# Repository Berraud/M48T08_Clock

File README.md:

# M48T08_Clock
Reloj con RTC M48T08 y ATMEGA328

Reloj diseñado en torno a un display 5-LT-02/02m, un RTC paralelo M48T08 y un ATMEGA328.

Procedimiento para setear la hora:

1) completar los registros con la fecha actual y la hora con algunos minutos a futuro

byte registros[8][8]={{0,0,0,1,1,0,0,1},//año 
                      {0,0,0,0,0,0,1,1},//mes
                      {0,0,1,0,0,0,1,1},//dia 
                      {0,0,0,0,0,1,1,0},//dia semana 
                      {0,0,0,1,0,0,0,1},//horas
                      {0,0,1,1,0,1,0,1},//minutos 
                      {1,0,0,0,0,0,0,0},//segundos
                      {0,0,0,0,0,0,0,0}};//cal
                      
Según hoja de datos el bit más significativo del registro segundos debe ser puesto en 1 primero y en 0 después para asegurar que el RTC comience a correr. Así que se puede cargar eso así sin configurar la hora, y después pasarlo a 0.

2) cargar código
3) Esperar a que sea la hora seteada en los registros y resetear el micro

Nota: No es nada elegante, podría hacerse mediante un menú por serie, o lo que sea, pero funciona y es rápido. Ver pines de conexión en el código. Lo hice con un Mega por disponibilidad de pines, pero podría hacerse también con un Nano

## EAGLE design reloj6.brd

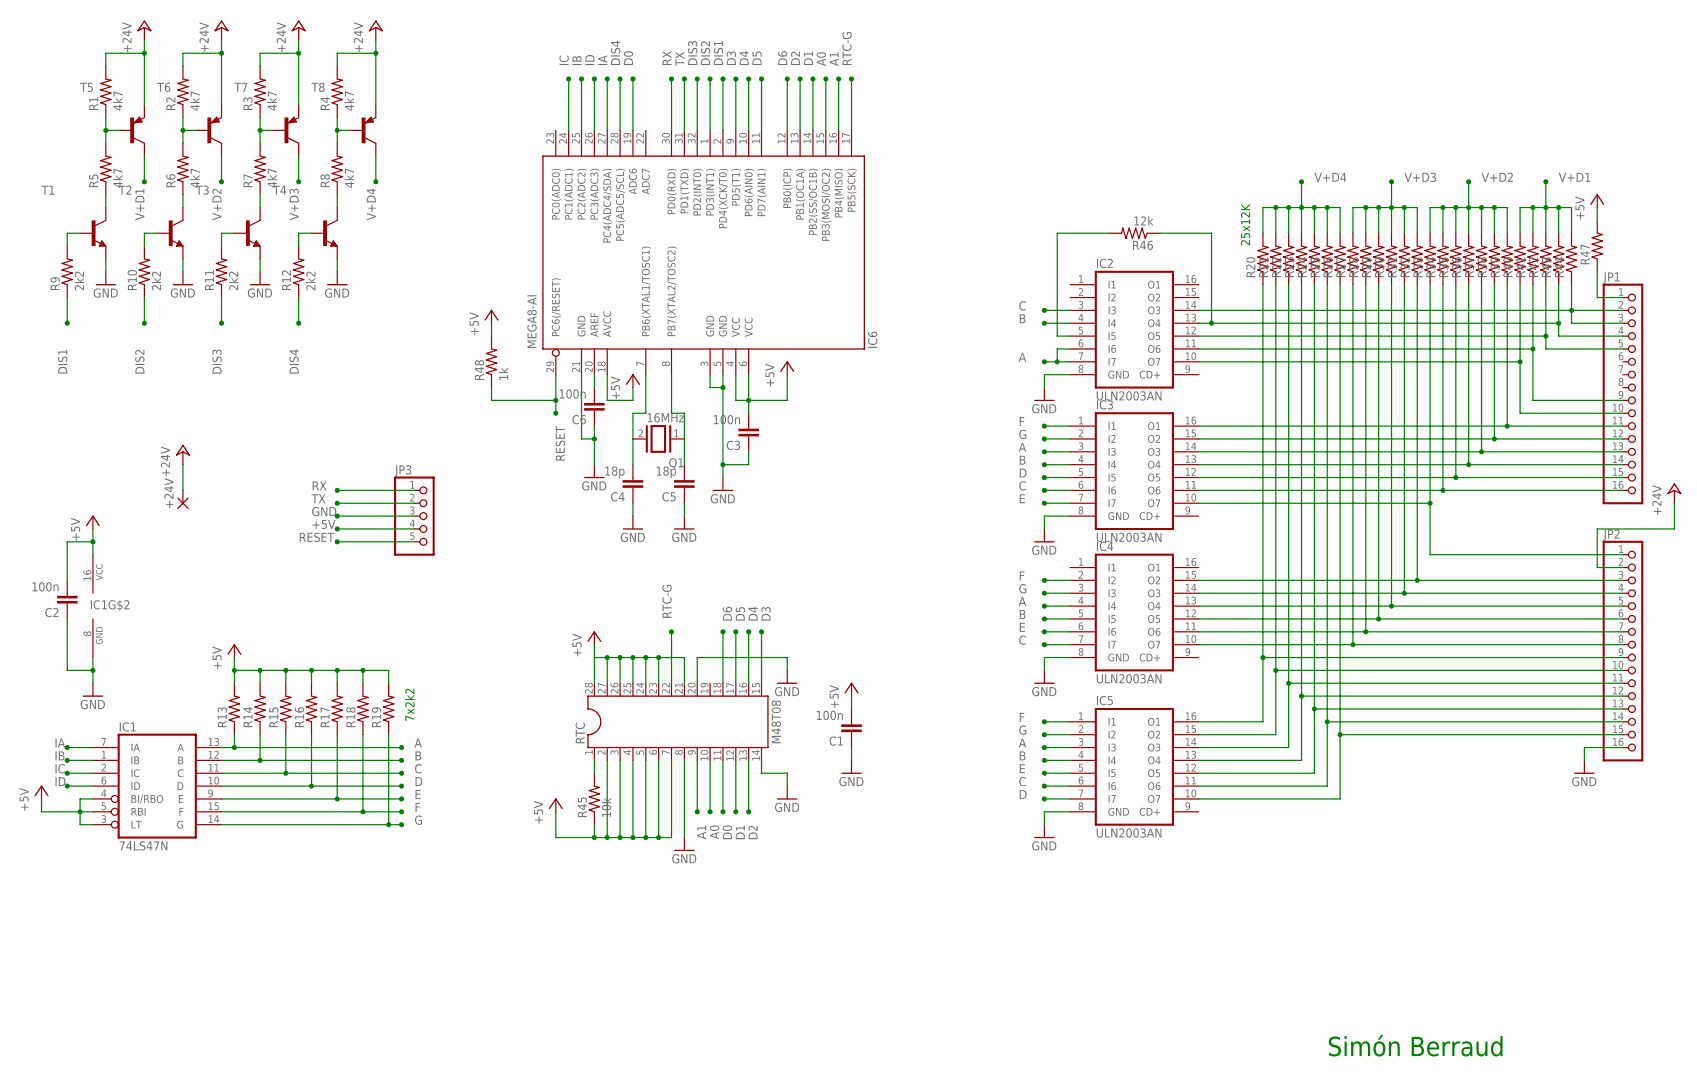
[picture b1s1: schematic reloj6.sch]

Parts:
+24V: 2,54/0,8
C1, C2, C3: 100n; C025-025X050
C4, C5: 18p; C0805K
C6: 100n; C0805K
IC1: 74LS47N; DIL16
IC2, IC3, IC4, IC5: ULN2003AN; DIL16
IC6: MEGA8-AI; TQFP32-08
JP1, JP2: PINHD-1X16; 1X16
JP3: PINHD-1X5; 1X05
Q1: 16MHz; QS
R1, R2, R3, R4, R5, R6, R7, R8: 4k7; 0207/7
R9, R10, R11, R12: 2k2; 0207/7
R13, R14, R15, R16, R17, R18, R19, R20, R21, R22, R23, R24, R25, R26, R27, R28, R29, R30, R31, R32, R33, R34, R35, R36, R37, R38, R39, R40, R41, R42, R43, R44: R-US_0207/7; 0207/7
R45: 10k; 0207/7
R46: 12k; 0207/7
R47: R-US_0411/12; 0411/12
R48: 1k; R1206
RTC: M48T08; DIL28-6
T1, T2, T3, T4: BC169-NPN-TO92-ECB; TO92-ECB
T5, T6, T7, T8: -PNP-TO92-ECB; TO92-ECB

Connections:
+5V: C1.2, C2.2, C3.2, IC1.3 (LT), IC1.4 (BI/RBO), IC1.5 (RBI), IC1.16 (VCC), IC6.4 (VCC), IC6.6 (VCC), IC6.18 (AVCC), JP3.4, R13.2, R14.2, R15.2, R16.2, R17.2, R18.2, R19.2, R45.1, R47.2, R48.2, RTC.2, RTC.3, RTC.4, RTC.5, RTC.6, RTC.7, RTC.21, RTC.23, RTC.24, RTC.25, RTC.26, RTC.27, RTC.28
+24V: +24V.1, JP2.2, R1.2, R2.2, R3.2, R4.2, T5.E, T6.E, T7.E, T8.E
A: IC1.13 (A), IC2.6 (I6), IC2.7 (I7), IC3.3 (I3), IC4.4 (I4), IC5.3 (I3), R13.1
A0: IC6.15 (PB3(MOSI/OC2)), RTC.10
A1: IC6.16 (PB4(MISO)), RTC.9
B: IC1.12 (B), IC2.4 (I4), IC3.4 (I4), IC4.5 (I5), IC5.4 (I4), R14.1
C: IC1.11 (C), IC2.3 (I3), IC3.6 (I6), IC4.7 (I7), IC5.6 (I6), R15.1
D: IC1.10 (D), IC3.5 (I5), IC5.7 (I7), R16.1
D0: IC6.19 (ADC6), RTC.11
D1: IC6.14 (PB2(SS/OC1B)), RTC.12
D2: IC6.13 (PB1(OC1A)), RTC.13
D3: IC6.9 (PD5(T1)), RTC.15
D4: IC6.10 (PD6(AIN0)), RTC.16
D5: IC6.11 (PD7(AIN1)), RTC.17
D6: IC6.12 (PB0(ICP)), RTC.18
DIS1: IC6.2 (PD4(XCK/T0)), R9.1
DIS2: IC6.1 (PD3(INT1)), R10.1
DIS3: IC6.32 (PD2(INT0)), R11.1
DIS4: IC6.28 (PC5(ADC5/SCL)), R12.1
E: IC1.9 (E), IC3.7 (I7), IC4.6 (I6), IC5.5 (I5), R17.1
F: IC1.15 (F), IC3.1 (I1), IC4.2 (I2), IC5.1 (I1), R18.1
G: IC1.14 (G), IC3.2 (I2), IC4.3 (I3), IC5.2 (I2), R19.1
GND: C1.1, C2.1, C3.1, C4.1, C5.1, C6.1, IC1.8 (GND), IC2.8 (GND), IC3.8 (GND), IC4.8 (GND), IC5.8 (GND), IC6.3 (GND), IC6.5 (GND), IC6.21 (GND), JP2.16, JP3.3, RTC.8, RTC.14, RTC.20, T1.E, T2.E, T3.E, T4.E
IA: IC1.7 (IA), IC6.27 (PC4(ADC4/SDA))
IB: IC1.1 (IB), IC6.25 (PC2(ADC2))
IC: IC1.2 (IC), IC6.24 (PC1(ADC1))
ID: IC1.6 (ID), IC6.26 (PC3(ADC3))
unnamed: R9.2, T1.B
unnamed: R10.2, T2.B
unnamed: R11.2, T3.B
unnamed: R12.2, T4.B
unnamed: JP1.1, R47.1
unnamed: R1.1, R5.2, T5.B
unnamed: R2.1, R6.2, T6.B
unnamed: R3.1, R7.2, T7.B
unnamed: R4.1, R8.2, T8.B
unnamed: R5.1, T1.C
unnamed: R6.1, T2.C
unnamed: R45.2, RTC.1
unnamed: R7.1, T3.C
unnamed: R8.1, T4.C
unnamed: C4.2, IC6.7 (PB6(XTAL1/TOSC1)), Q1.2
unnamed: IC5.16 (O1), JP2.9, R20.1
unnamed: C5.2, IC6.8 (PB7(XTAL2/TOSC2)), Q1.1
unnamed: C6.2, IC6.20 (AREF)
unnamed: IC3.13 (O4), JP1.14, R36.1
unnamed: IC3.11 (O6), JP1.16, R34.1
unnamed: IC4.14 (O3), JP2.4, R31.1
unnamed: IC4.12 (O5), JP2.6, R29.1
unnamed: IC4.11 (O6), JP2.7, R28.1
unnamed: IC2.13 (O4), JP1.4, R43.1, R46.1
unnamed: IC2.5 (I5), R46.2
unnamed: IC2.10 (O7), JP1.10, R40.1
unnamed: IC2.11 (O6), JP1.9, R41.1
unnamed: IC2.12 (O5), JP1.5, R42.1
unnamed: IC2.14 (O3), JP1.2, JP1.3, R44.1
unnamed: IC3.16 (O1), JP1.11, R39.1
unnamed: IC3.15 (O2), JP1.12, R38.1
unnamed: IC3.14 (O3), JP1.13, R37.1
unnamed: IC3.12 (O5), JP1.15, R35.1
unnamed: IC3.10 (O7), JP2.1, R33.1
unnamed: IC4.15 (O2), JP2.3, R32.1
unnamed: IC4.13 (O4), JP2.5, R30.1
unnamed: IC4.10 (O7), JP2.8, R27.1
unnamed: IC5.15 (O2), JP2.10, R21.1
unnamed: IC5.14 (O3), JP2.11, R22.1
unnamed: IC5.13 (O4), JP2.12, R23.1
unnamed: IC5.12 (O5), JP2.13, R24.1
unnamed: IC5.11 (O6), JP2.14, R25.1
unnamed: IC5.10 (O7), JP2.15, R26.1
RESET: IC6.29 (PC6(/RESET)), JP3.5, R48.1
RTC-G: IC6.17 (PB5(SCK)), RTC.22
RX: IC6.30 (PD0(RXD)), JP3.1
TX: IC6.31 (PD1(TXD)), JP3.2
V+D1: R40.2, R41.2, R42.2, R43.2, R44.2, T5.C
V+D2: R33.2, R34.2, R35.2, R36.2, R37.2, R38.2, R39.2, T6.C
V+D3: R27.2, R28.2, R29.2, R30.2, R31.2, R32.2, T7.C
V+D4: R20.2, R21.2, R22.2, R23.2, R24.2, R25.2, R26.2, T8.C

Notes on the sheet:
25x12K
7x2k2
Simón Berraud

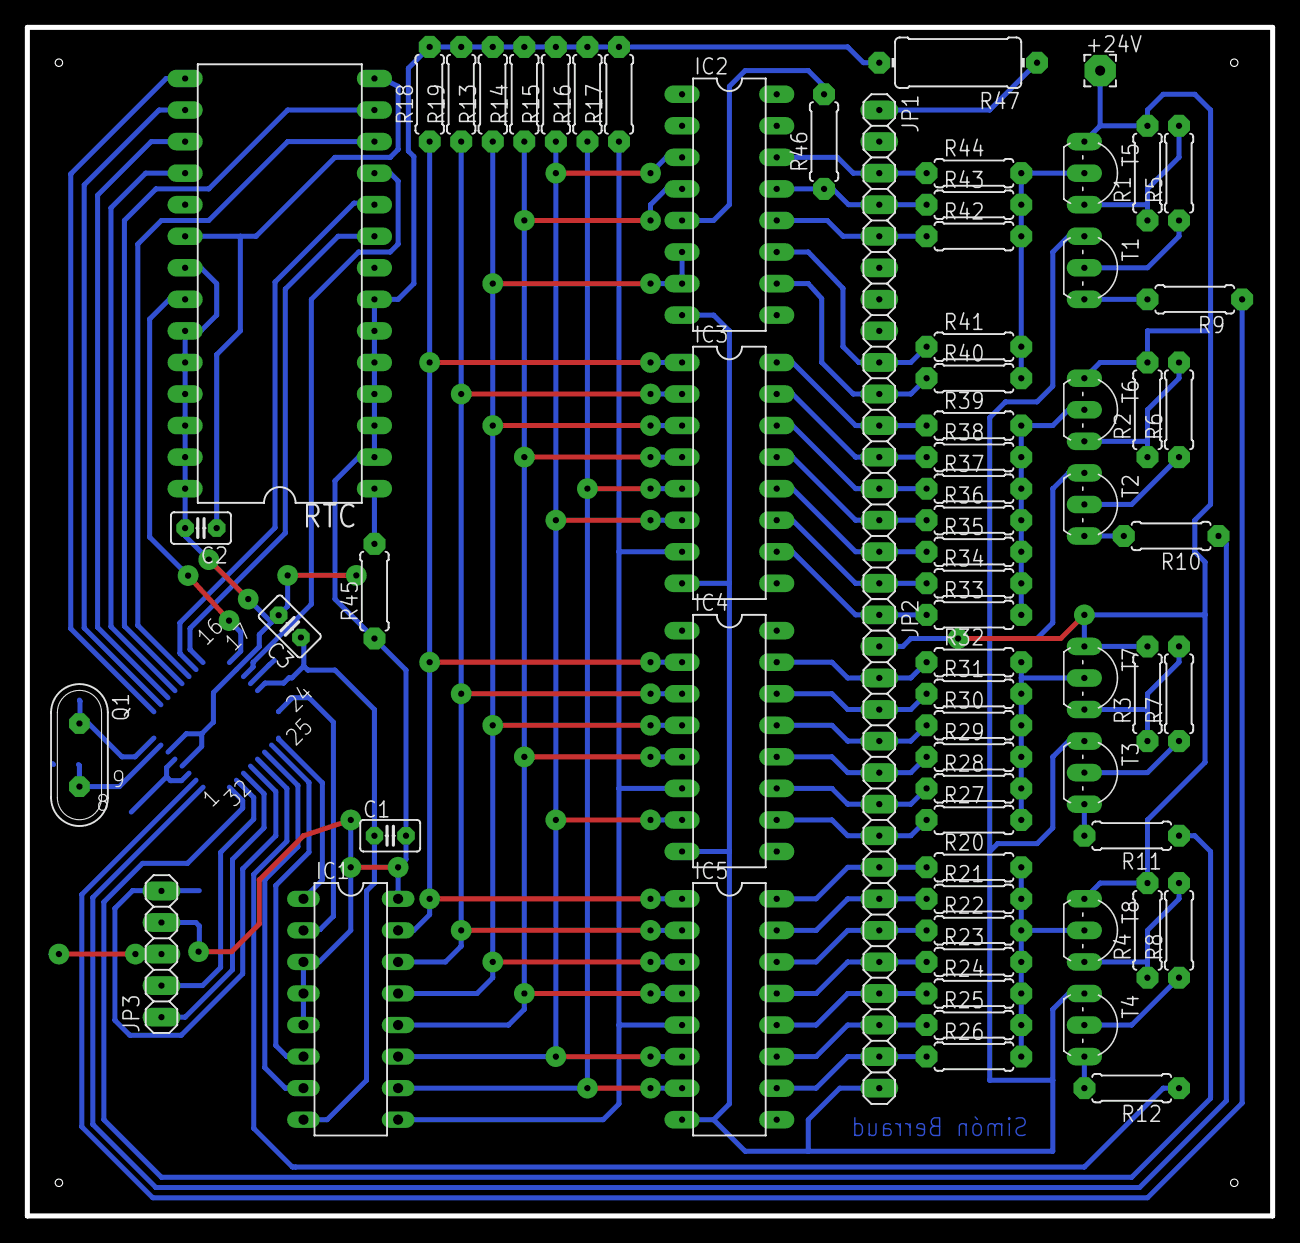
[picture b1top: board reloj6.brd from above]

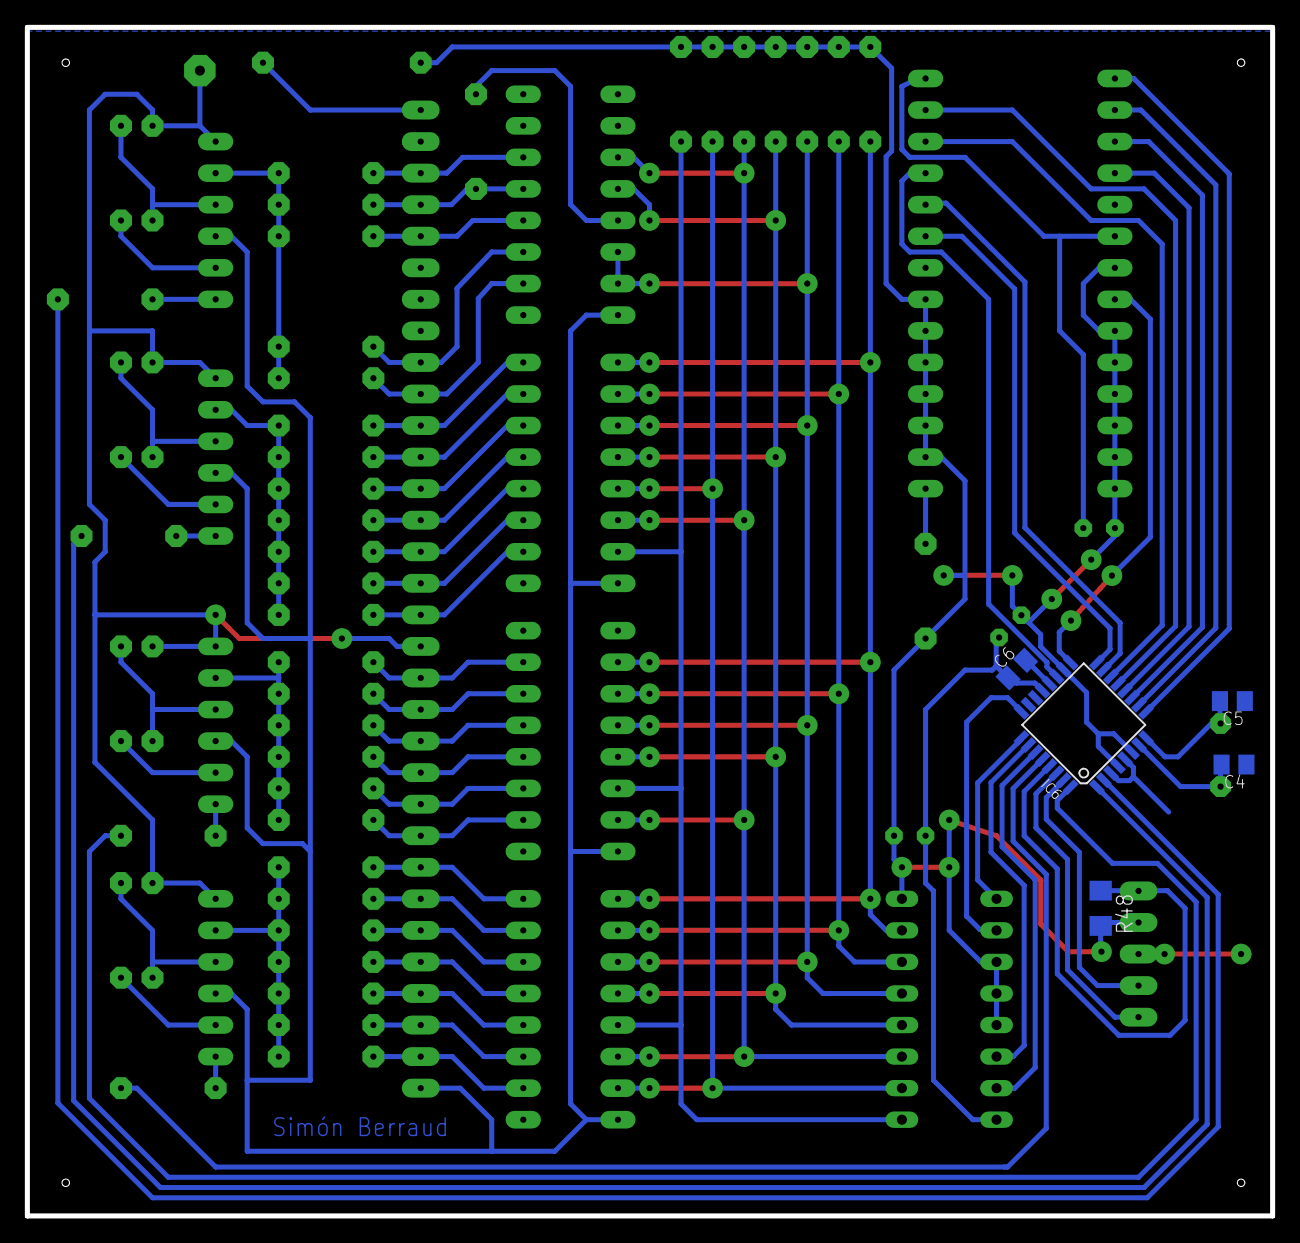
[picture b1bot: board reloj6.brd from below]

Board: 2 copper layers, 100.2 x 95.7 mm, 74 parts (5 on the bottom side), 78 nets.

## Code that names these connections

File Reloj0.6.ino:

#include <FrequencyTimer2.h>


int timerRTC=100;
int d0=0;
int d1=0;
int d2=0;
int d3=0;
byte setadd=0;
byte datolisto=0;
int reg=0;

byte registros[3][8]={{0,0,0,0,0,0,0,0},//horas
                      {0,0,0,0,0,0,0,0},//minutos
                      {0,0,0,0,0,0,0,0}};//segundos

byte horasC[24][8]={{0,0,0,0,0,0,0,0},//00 lo necesito para setear PM
                    {0,0,0,0,0,0,0,1},//01
                    {0,0,0,0,0,0,1,0},//02
                    {0,0,0,0,0,0,1,1},//03
                    {0,0,0,0,0,1,0,0},//04
                    {0,0,0,0,0,1,0,1},//05
                    {0,0,0,0,0,1,1,0},//06
                    {0,0,0,0,0,1,1,1},//07
                    {0,0,0,0,1,0,0,0},//08
                    {0,0,0,0,1,0,0,1},//09
                    {0,0,0,1,0,0,0,0},//10
                    {0,0,0,1,0,0,0,1},//11
                    {0,0,0,1,0,0,1,0},//12 lo necesito para setear PM
                    {0,0,0,1,0,0,1,1},//13
                    {0,0,0,1,0,1,0,0},//14
                    {0,0,0,1,0,1,0,1},//15
                    {0,0,0,1,0,1,1,0},//16
                    {0,0,0,1,0,1,1,1},//17
                    {0,0,0,1,1,0,0,0},//18
                    {0,0,0,1,1,0,0,1},//19
                    {0,0,1,0,0,0,0,0},//20
                    {0,0,1,0,0,0,0,1},//21
                    {0,0,1,0,0,0,1,0},//22
                    {0,0,1,0,0,0,1,1}};//23


byte PM=0;
byte minutoCero=0;
byte puntitos=0;

byte regHoras[12]={0,0,0,0,0,0,0,0,0,0,0,0}; //a la hora de comparar las horas evalúo si la hora actual es disinta a los registros para corregirla
byte simbolo[4]={0,0,0,0};

int dir[3] = {12, 11}; //A1 A0
int datos[7] ={8,7,6,5,9,10,20}; //D6 D0

#define G 13

byte col = 0;
byte leds[4][4]; //en esta actualizar el dato a mostrar en display

// pin[xx] on led matrix connected to nn on Arduino (-1 is dummy to make array start at pos 1)
int pins[9]= {-1, 4, 3, 2, 19, 17, 15, 16, 18};//dummy dis1 - dis4/ ID-IA

// col[xx] of leds = pin yy on led matrix
int cols[4] = {pins[1], pins[2], pins[3], pins[4]};//dis1,dis2,dis3,dis4

// row[xx] of leds = pin yy on led matrix
int rows[4] = {pins[5], pins[6], pins[7], pins[8]};//ID,IC,IB,IA

int pattern[4] = {0,0,0,0};

void setup() {
  // sets the pins as output
  for (int i = 1; i <= 8; i++) {
    pinMode(pins[i], OUTPUT);
  }

  for (int i = 0; i < 2; i++) {//este
    pinMode(dir[i], OUTPUT);
  }

  for (int i = 0; i < 7; i++) {//y este
    pinMode(datos[i], INPUT);
  }

  // set up cols and rows
  for (int i = 1; i <= 4; i++) {
    digitalWrite(cols[i - 1], LOW);
  }

  for (int i = 1; i <= 4; i++) {
    digitalWrite(rows[i - 1], LOW);
  }

  clearLeds();

  // Turn off toggling of pin 11
  FrequencyTimer2::disable();
  // Set refresh rate (interrupt timeout period)
  FrequencyTimer2::setPeriod(2000);
  // Set interrupt routine to be called
  FrequencyTimer2::setOnOverflow(display);

 
  Serial.begin(9600);

  //------------Lectura inicial para cuando reinicia. Después sólo leo si min=00
  LeerMinutos();
  LeerHoras();
  CoregirHora();
  CargarMatrizLed();
}

void loop() {
    
    if(!timerRTC)
    {
      LeerMinutos();
      if(minutoCero)
        {
        LeerHoras();
        CoregirHora();  
        }
      LeerSegundos();
      if(registros[2][7]==1)
        puntitos=1;
      else
        puntitos=0;

      //tres variables que determinan el código: PM, puntito y registros[0][3]
      
      CorreccionSimbolos(); //a 1 / b=AM/PM c=puntitos
      
        
      CargarMatrizLed();

      timerRTC=100;
    }
    
}

void LeerMinutos()
{   
  digitalWrite(G,1);
  
  //dirección
  digitalWrite(dir[0],1);//A1 
  digitalWrite(dir[1],0);//A0 
  
 
  digitalWrite(G,0);
  minutoCero=1;
  for(int i=0;i<6;i++)
      {
      registros[1][i+1]=digitalRead(datos[i]);
      if(registros[1][i+1]==1) minutoCero=0;//si encuentro un 1 en el registro de minutos quiere decir que no es cero, y minutoCero pasa a 0, sino queda en 1;
      }
      if(analogRead(datos[6])>512)
        {
        registros[1][7]=1;
        minutoCero=0; //acá también xq el último bit lo leo analógicamente
        }
      else
        registros[1][7]=0;
}

void LeerHoras()
{
   digitalWrite(G,1);
  
  //dirección
  digitalWrite(dir[0],1);//A1 1FFBh Horas
  digitalWrite(dir[1],1);//A0 
  
  
  digitalWrite(G,0);
  
  for(int i=0;i<6;i++)
      registros[0][i+1]=digitalRead(datos[i]);

      if(analogRead(datos[6])>512)
        registros[0][7]=1;
      else
        registros[0][7]=0;
}

void LeerSegundos()
{
  digitalWrite(G,1);
  
  digitalWrite(dir[0],0);//A1 10 1FF9h segundos
  digitalWrite(dir[1],1);//A0 11
  
  
  digitalWrite(G,0);
   //sólo me interesa el bit menos significativo para titilar los puntitos
  
  if(analogRead(datos[6])>512)
    registros[2][7]=1;
  else
    registros[2][7]=0;
}

void CoregirHora()
{
  //verificar si son más de las 12
  for(int j=0; j<12; j++)
    {
    regHoras[j]=1; //lo pongo en 1. Si la comparación da que son distintos lo paso a cero. El que queda en 1 es el correcto
    
    for(int i=0; i<8; i++)
      {
        if(registros[0][i]!=horasC[j+12][i]) 
        {
          regHoras[j]=0; //registros[0] hora vs 12/23
        }
      }
    }
  //setear PM
  
  PM=0;
  
  for(int i=0;i<12;i++)
    if(regHoras[i]==1) PM=1;
    
  //corregir a la hora en formato 12hs
  for(int i=1;i<12;i++) //si es 12 no lo corrijo
    if(regHoras[i]) //si encontré una a corregir regHoras[1]=13 
      for(int j=0;j<8;j++) //actualizo todos los bits del registro hora
        registros[0][j]=horasC[i][j];
}

void CorreccionSimbolos()
{
  //cargar símbolos en primer digito
  if(!registros[0][3] && !PM && !puntitos) //1010
    {
    simbolo[0]=1;
    simbolo[1]=0;
    simbolo[2]=1;
    simbolo[3]=0;
    }
   if(!registros[0][3] && !PM && puntitos) //1011
    {
    simbolo[0]=1;
    simbolo[1]=0;
    simbolo[2]=1;
    simbolo[3]=1;
    }
     if(!registros[0][3] && PM && !puntitos) //1100
    {
    simbolo[0]=1;
    simbolo[1]=1;
    simbolo[2]=0;
    simbolo[3]=0;
    }
     if(!registros[0][3] && PM && puntitos) //0100
    {
    simbolo[0]=0;
    simbolo[1]=1;
    simbolo[2]=0;
    simbolo[3]=0;
    }
     if(registros[0][3] && !PM && !puntitos) //1101
    {
    simbolo[0]=1;
    simbolo[1]=1;
    simbolo[2]=0;
    simbolo[3]=1;
    }
     if(registros[0][3] && !PM && puntitos) //0101
    {
    simbolo[0]=0;
    simbolo[1]=1;
    simbolo[2]=0;
    simbolo[3]=1;
    }
     if(registros[0][3] && PM && !puntitos) //0010
    {
    simbolo[0]=0;
    simbolo[1]=0;
    simbolo[2]=1;
    simbolo[3]=0;
    }
     if(registros[0][3] && PM && puntitos) //0000
    {
    simbolo[0]=0;
    simbolo[1]=0;
    simbolo[2]=0;
    simbolo[3]=0;
    }
}

void CargarMatrizLed()
{
  for (int j = 0; j < 4; j++) {
      leds[j][0] = simbolo[j];
      leds[j][1] = registros[0][4+j];
      leds[j][2] = registros[1][j];
      leds[j][3] = registros[1][4+j];
      }
}

void clearLeds() {
  // Clear display array
  for (int i = 0; i < 4; i++) {
    for (int j = 0; j < 4; j++) {
      leds[i][j] = 0; //leds es la variable en donde están almacenados los datos a sacar al momento de la interrupción
    }
  }
}


// Interrupt routine
void display() {
  digitalWrite(cols[col], LOW);  // Turn whole previous column off
  col++;
  if (col == 4) 
    {
    col = 0;
    }
  for (int row = 0; row < 4; row++) 
    {
    if (leds[row][col] == 1) 
      {
      digitalWrite(rows[row], HIGH);  // Turn on this led
      //Serial.print("0");
      }
    else 
    {
      digitalWrite(rows[row], LOW); // Turn off this led
      //Serial.print("1");
      }
    }
  digitalWrite(cols[col], HIGH); // Turn whole column on at once (for equal lighting times)
  
  //------contadores
  
  if(timerRTC) timerRTC--;
}
